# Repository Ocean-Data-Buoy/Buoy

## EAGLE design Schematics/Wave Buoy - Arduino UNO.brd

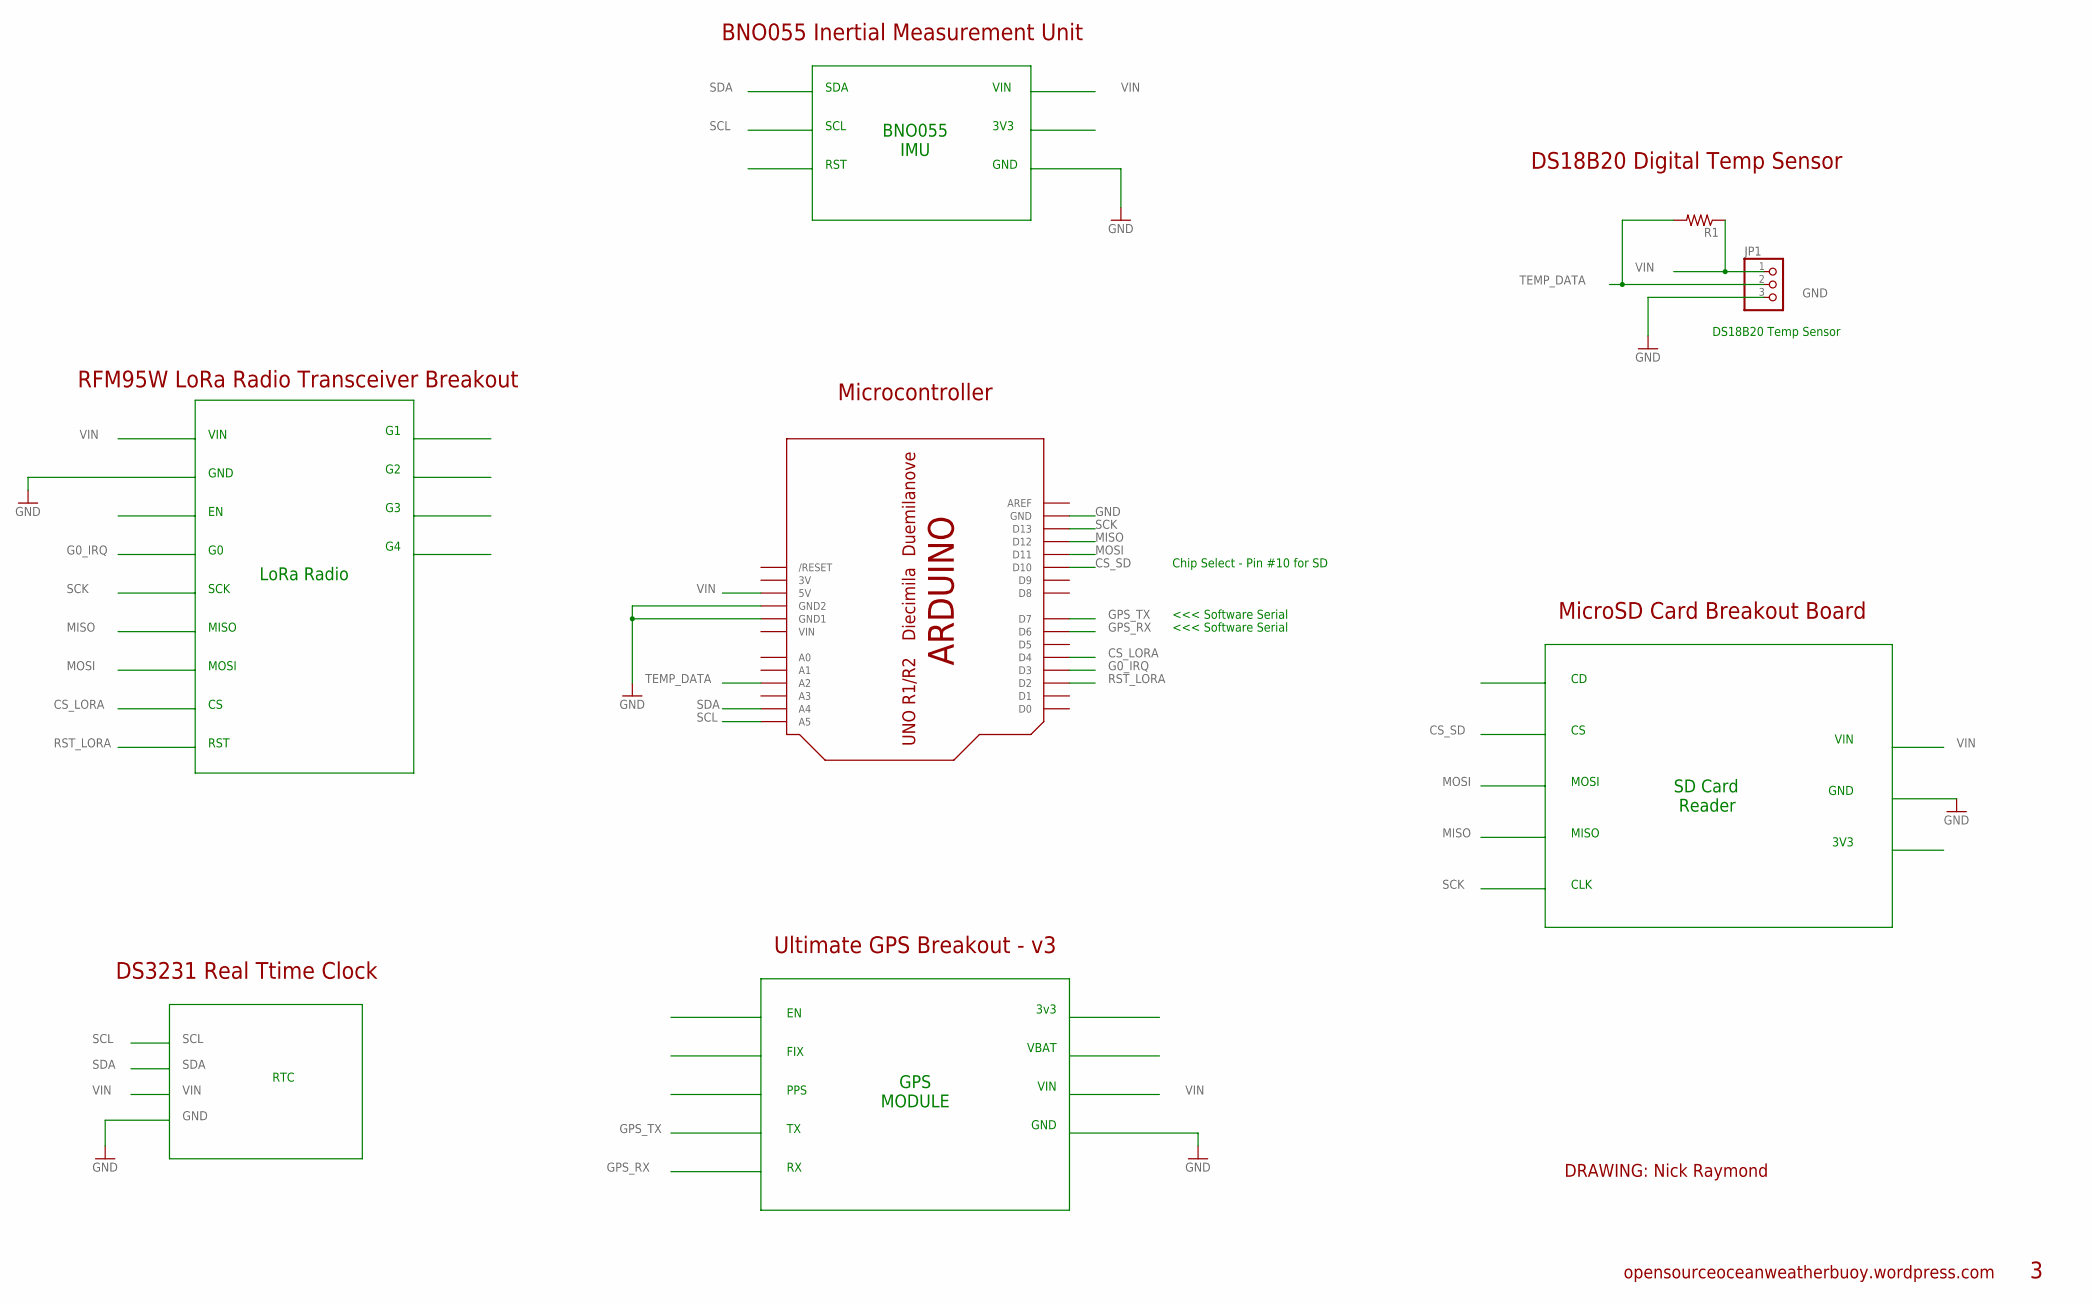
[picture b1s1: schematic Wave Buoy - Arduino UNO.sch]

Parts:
JP1: PINHD-1X3CB; 1X03-CLEANBIG
R1: FLIPFLOP-RES; 0805-THM
U$1: ARDUINO-NODIM

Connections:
3V: U$1.3V
CS_LORA: U$1.D4
CS_SD: U$1.D10
G0_IRQ: U$1.D3
GND: JP1.3, U$1.GND, U$1.GND1, U$1.GND2
GPS_RX: U$1.D6
GPS_TX: U$1.D7
MISO: U$1.D12
MOSI: U$1.D11
RST_LORA: U$1.D2
SCK: U$1.D13
SCL: U$1.A5
SDA: U$1.A4
TEMP_DATA: JP1.2, R1.2, U$1.A2
VIN: JP1.1, R1.1, U$1.5V, U$1.VIN

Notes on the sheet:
SDA
SCL
RST
VIN
3V3
GND
BNO055 IMU
LoRa Radio
SCK
MISO
MOSI
3v3
VBAT
FIX
PPS
GPS MODULE
CLK
SD Card Reader
Chip Select - Pin #10 for SD
RTC
<<< Software Serial
DS18B20 Temp Sensor
DRAWING: Nick Raymond
Ultimate GPS Breakout - v3
Microcontroller
RFM95W LoRa Radio Transceiver Breakout
BNO055 Inertial Measurement Unit
DS3231 Real Ttime Clock
DS18B20 Digital Temp Sensor
MicroSD Card Breakout Board
opensourceoceanweatherbuoy.wordpress.com

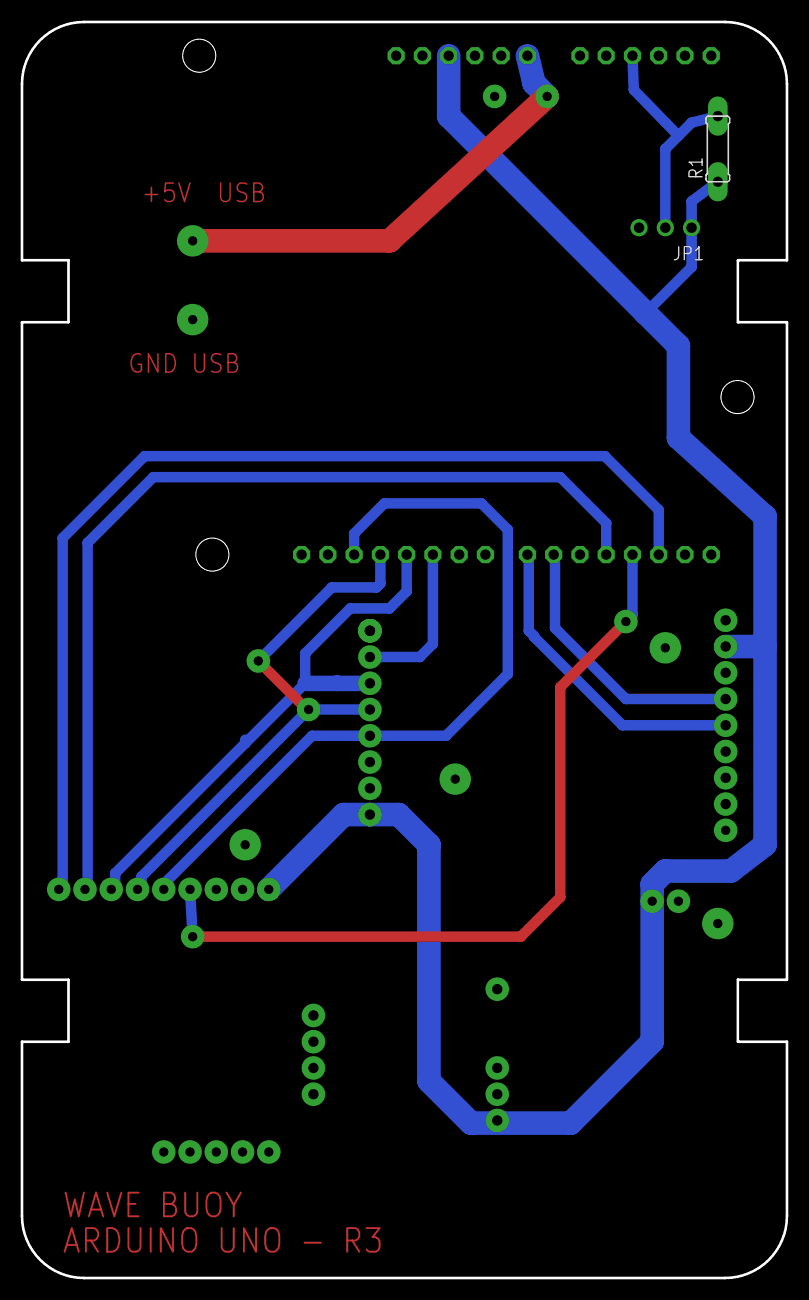
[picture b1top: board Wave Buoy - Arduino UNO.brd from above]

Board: 2 copper layers, 74.0 x 121.5 mm, 3 parts (1 on the bottom side), 3 nets.

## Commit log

2018-06-03 adding information
2018-06-03 adding CAD files
